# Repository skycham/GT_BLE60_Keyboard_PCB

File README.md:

# GT_BLE60_Keyboard_PCB
A 60% bluetooth keyboard PCB by Kicad, Schematic fork of https://github.com/Lotlab/BLE60-keyboard  
一个采用Kicad设计制作的60%蓝牙键盘PCB，原理图参考Lotlab的蓝牙键盘，并基于GH60制作。

**已经验证完成，可以直接打板制作**

using nRF51822 and CH554(or CH552).  
使用NRF51822 与 CH554（或者CH552）芯片

Firmware Source Code/固件源码: [nrf51822-keyboard](https://github.com/genokolar/nrf51822-keyboard/tree/GT-BLE60)

License: CC-BY-SA

More description/详细信息在此查看：[http://genokolar.github.io/blog/201903](http://genokolar.github.io/blog/201903)

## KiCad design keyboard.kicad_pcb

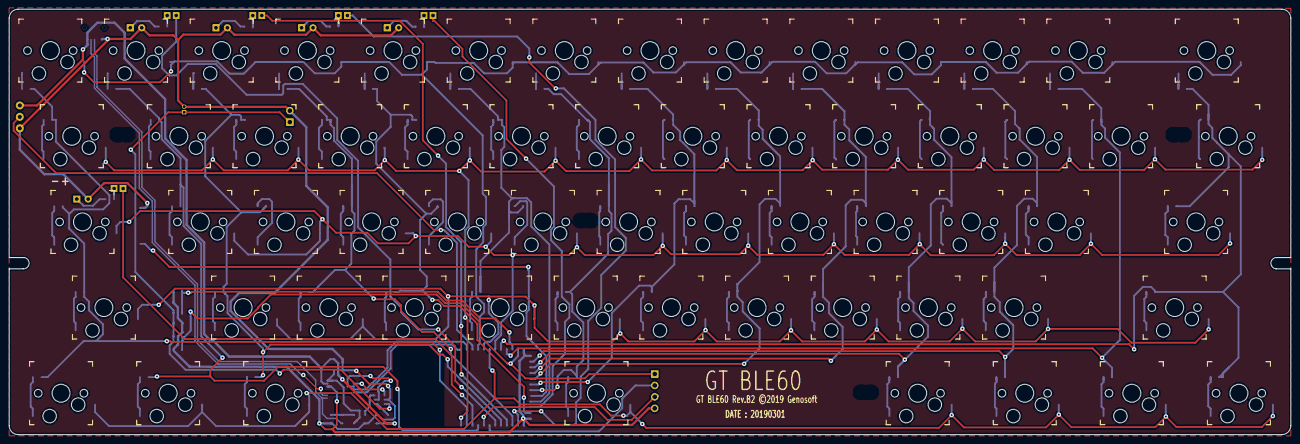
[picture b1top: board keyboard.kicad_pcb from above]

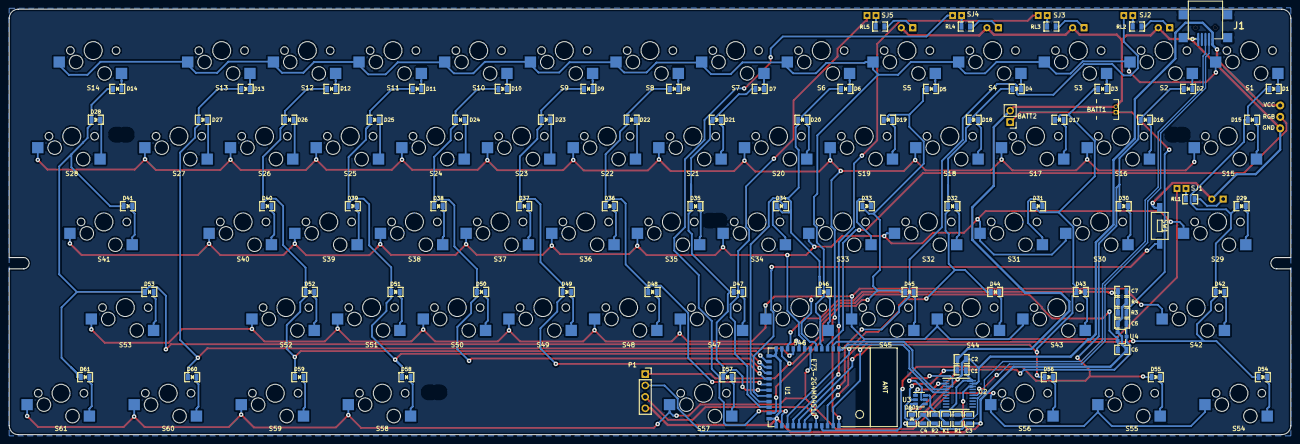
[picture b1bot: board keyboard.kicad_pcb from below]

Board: 2 copper layers, 285.0 x 94.6 mm, 168 parts (98 on the bottom side), 114 nets.

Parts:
BATT1: PinHeader_2x1.25mm
BATT2: BATT; PinHeader_1x02_P2.54mm_Vertical
C1, C2: 0.1uF; 0805C
C3: NC/47pF; 0805C
C4, C5, C6: 1uF; 0805C
C7: 10nF; 0805C
D1, D2, D3, D4, D5, D6, D7, D8, D9, D10, D11, D12, D13, D14, D15, D16, D17, D18, D19, D20, D21, D22, D23, D24, D25, D26, D27, D28, D29, D30, D31, D32, D33, D34, D35, D36, D37, D38, D39, D40, D41, D42, D43, D44, D45, D46, D47, D48, D49, D50, D51, D52, D53, D54, D55, D56, D57, D58, D59, D60, D61: 1N4148; 0805D
D101: SS14; 0805D
GND: CONN_1; pad
HOLE1, HOLE2, HOLE3, HOLE4: VAL; PKRH-2
J1: USBMINI_B05; 67503
K1: DownloadKey; 0805R
LED1, LED2, LED3, LED4, LED5: LED; MX1A-led
LOGO1: LOGO; GTBLE60
LOGO2: LOGO; Bluetooth
P1: SWD; PinSocket_1x04_P2.54mm_Vertical
R1: 10K; 0805R
R2: 4.7K; 0805R
R3: 10M; 0805R
R4: 2.2M; 0805R
RGB: CONN_1; pad
RL1, RL2, RL3, RL4, RL5: 300; 0805R
S1, S2, S3, S4, S5, S6, S7, S8, S9, S10, S11, S12, S13, S14, S15, S16, S17, S18, S19, S20, S21, S22, S23, S24, S25, S26, S27, S28, S29, S30, S31, S32, S33, S34, S35, S36, S37, S38, S39, S40, S41, S42, S43, S44, S45, S46, S47, S48, S49, S50, S51, S52, S53, S54, S55, S56, S57, S58, S59, S60, S61: MX1A; Kailh-3d-noled
SJ1, SJ2, SJ3, SJ4, SJ5: SOLDER_JUMPER; 2_Pin_Jumper
SW1: Bootloader Button; Switch
U1: E73-2G4M04S1D
U2: CH552T
U3: TP4057; SOT-23-6
U4: XC6206P30; SOT-23
VCC: CONN_1; pad

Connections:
3V3: C6.1, P1.1, U1.11, U4.2
/DFU: SW1.2, U1.20
/RGB: RGB.1, U1.3
/caps_led: SJ1.1, U1.34
/col1: D1.1, D15.1, D29.1, D42.1, D54.1, U1.35
/col2: D2.1, D16.1, D30.1, D55.1, U1.33
/col3: D3.1, D17.1, D31.1, D43.1, D56.1, U1.29
/col4: D4.1, D18.1, D32.1, D44.1, U1.27
/col5: D5.1, D19.1, D33.1, D45.1, U1.23
/col6: D6.1, D20.1, D34.1, D46.1, U1.21
/col7: D7.1, D21.1, D35.1, D47.1, D57.1, U1.19
/col8: D8.1, D22.1, D36.1, D48.1, U1.18
/col9: D9.1, D23.1, D37.1, D49.1, U1.17
/col10: D10.1, D24.1, D38.1, D50.1, U1.16
/col11: D11.1, D25.1, D39.1, D51.1, D58.1, U1.15
/col12: D12.1, D26.1, D40.1, D52.1, D59.1, U1.14
/col13: D13.1, D27.1, D60.1, U1.9
/col14: D14.1, D28.1, D41.1, D53.1, D61.1, U1.8
/led1: SJ2.1, U1.30
/led2: SJ3.1, U1.28
/led3: SJ4.1, U1.26
/led4: SJ5.1, U1.22
/row1: S1.1, S2.1, S3.1, S4.1, S5.1, S6.1, S7.1, S8.1, S9.1, S10.1, S11.1, S12.1, S13.1, S14.1, U1.4
/row2: S15.1, S16.1, S17.1, S18.1, S19.1, S20.1, S21.1, S22.1, S23.1, S24.1, S25.1, S26.1, S27.1, S28.1, U1.36
/row3: S29.1, S30.1, S31.1, S32.1, S33.1, S34.1, S35.1, S36.1, S37.1, S38.1, S39.1, S40.1, S41.1, U1.7
/row4: S42.1, S43.1, S44.1, S45.1, S46.1, S47.1, S48.1, S49.1, S50.1, S51.1, S52.1, S53.1, U1.5
/row5: S54.1, S55.1, S56.1, S57.1, S58.1, S59.1, S60.1, S61.1, U1.6
ADC1: C7.1, R3.2, R4.1, U1.10
BATT: BATT1.1, BATT2.1, C5.1, R3.1, U3.3, U4.3
CHRG: U2.2, U3.1
DCLK: P1.3, U1.32
DIO: P1.2, U1.31
GND: BATT1.2, BATT2.2, C1.2, C2.2, C3.2, C4.2, C5.2, C6.2, C7.2, GND.1, J1.5, LED1.1, LED2.1, LED3.1, LED4.1, LED5.1, P1.4, R2.2, R4.2, SW1.1, U1.12, U1.13, U1.24, U1.25, U2.18, U3.2, U4.1
unnamed: C3.1, K1.1, R1.1
unnamed: D1.2, S1.2
unnamed: D2.2, S2.2
unnamed: D3.2, S3.2
unnamed: D4.2, S4.2
unnamed: D5.2, S5.2
unnamed: D6.2, S6.2
unnamed: D7.2, S7.2
unnamed: D8.2, S8.2
unnamed: D9.2, S9.2
unnamed: D10.2, S10.2
unnamed: D11.2, S11.2
unnamed: D12.2, S12.2
unnamed: D13.2, S13.2
unnamed: D14.2, S14.2
unnamed: D15.2, S15.2
unnamed: D16.2, S16.2
unnamed: D17.2, S17.2
unnamed: D18.2, S18.2
unnamed: D19.2, S19.2
unnamed: D20.2, S20.2
unnamed: D21.2, S21.2
unnamed: D22.2, S22.2
unnamed: D23.2, S23.2
unnamed: D24.2, S24.2
unnamed: D25.2, S25.2
unnamed: D26.2, S26.2
unnamed: D27.2, S27.2
unnamed: D28.2, S28.2
unnamed: D29.2, S29.2
unnamed: D30.2, S30.2
unnamed: D31.2, S31.2
unnamed: D32.2, S32.2
unnamed: D33.2, S33.2
unnamed: D34.2, S34.2
unnamed: D35.2, S35.2
unnamed: D36.2, S36.2
unnamed: D37.2, S37.2
unnamed: D38.2, S38.2
unnamed: D39.2, S39.2
unnamed: D40.2, S40.2
unnamed: D41.2, S41.2
unnamed: D42.2, S42.2
unnamed: D43.2, S43.2
unnamed: D44.2, S44.2
unnamed: D45.2, S45.2
unnamed: D46.2, S46.2
unnamed: D47.2, S47.2
unnamed: D48.2, S48.2
unnamed: D49.2, S49.2
unnamed: D50.2, S50.2
unnamed: D51.2, S51.2
unnamed: D52.2, S52.2
unnamed: D53.2, S53.2
unnamed: D54.2, S54.2
unnamed: D55.2, S55.2
unnamed: D56.2, S56.2
unnamed: D57.2, S57.2
unnamed: D58.2, S58.2
unnamed: D59.2, S59.2
unnamed: D60.2, S60.2
unnamed: D61.2, S61.2
unnamed: D101.2, U3.4
unnamed: LED1.2, RL1.2
unnamed: LED2.2, RL2.1
unnamed: LED3.2, RL3.1
unnamed: LED4.2, RL4.1
unnamed: LED5.2, RL5.1
unnamed: R2.1, U3.6
unnamed: RL1.1, SJ1.2
unnamed: RL2.2, SJ2.2
unnamed: RL3.2, SJ3.2
unnamed: RL4.2, SJ4.2
unnamed: RL5.2, SJ5.2
RXD: U1.2, U2.4
STBY: U2.3, U3.5
TXD: U1.1, U2.5
UD+: J1.3, R1.2, U2.14
UD-: J1.2, U2.15
V33: C1.1, K1.2, U2.20
VCC: C2.1, C4.1, D101.1, J1.1, U2.19, VCC.1

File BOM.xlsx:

Id | 代号 | 封装 | 数量 | 名称 | 备注说明
1 | BATT1 | PinHeader_2x1.25mm | 1 | PinHeader_2x1.25mm | 锂电池接口
2 | C1,C2 | 0805C | 2 | 0.1uF
3 | C3 | 0805C | 1 | NC/47pF | 可不用焊接
4 | C4,C5,C6 | 0805C | 3 | 1uF
5 | C7 | 0805C | 1 | 10nF
6 | D101 | 0805D | 1 | SS14 | 肖特基二极管，锂电池芯片TP4057用
7 | D1-D61 | 0805D | 61 | 1N4148 | 全键防冲二极管，焊接注意方向
8 | J1 | 67503 | 1 | USBMINI_B05 | MINI USB接口
10 | K1 | 0805R | 1 | DownloadKey | 不用焊接元件，用于短接进入CH552的刷写模式
11 | LED1-LED6 | MX1A-led | 6 | LED | 指示灯（除CAPS外属于预留）
12 | R1 | 0805R | 1 | 10K | 接CH552的3.3V电源引脚，以便短接刷机
13 | R2 | 0805R | 1 | 4.7K | 建议2K-5K 之间，其中2K时充电电流为400ma，5K时充电电流为200ma，详细内容参看TP4057技术手册
14 | R3 | 0805R | 1 | 10M | 精度重要，以此为参考检测锂电池电量
15 | R4 | 0805R | 1 | 2.2M | 精度重要，以此为参考检测锂电池电量
16 | RL1-RL5 | 0805R | 5 | 300R | 指示灯灯阻
17 | S1-S61 | Kailh-3d-noled | 61 | MX1A | 机械键盘轴体
18 | U1 | E73-2G4M04S1D | 1 | E73-2G4M04S1D | 蓝牙主控模块
19 | U2 | CH552T | 1 | CH552T | USB芯片
20 | U3 | SOT-23-6 | 1 | TP4057 | 锂电池充电芯片
21 | U4 | SOT-23 | 1 | XC6206P30 | 3.3V稳压，用于主控供电
22 | SW1 | Switch | 1 | Bootloader Button | 进入刷机模式的按钮

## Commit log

2019-02-14 init
2019-03-01 修正原理图两处错误，添加Bootloader按钮
    版本设定为B2版本，修正了原理图的两处错误，添加了Bootloadler按钮便于进入DFU刷机模式。
2019-03-04 添加SWD接口丝印

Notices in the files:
keyboard.kicad_pcb:
©2018 Genosoft
GT BLE60 Rev.B2 ©2019 Genosoft
